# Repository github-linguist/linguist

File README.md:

# Linguist

This library is used on GitHub.com to detect blob languages, ignore binary or vendored files, suppress generated files in diffs, and generate language breakdown graphs.

## Documentation

- [How Linguist works](/docs/how-linguist-works.md)
- [Change Linguist's behaviour with overrides](/docs/overrides.md)
- [Troubleshooting](/docs/troubleshooting.md)
- [Contributing guidelines](CONTRIBUTING.md)

## Installation

Install the gem:

```bash
gem install github-linguist
```

### Dependencies

Linguist is a Ruby library so you will need a recent version of Ruby installed.
There are known problems with the macOS/Xcode supplied version of Ruby that causes problems installing some of the dependencies.
Accordingly, we highly recommend you install a version of Ruby using Homebrew, `rbenv`, `rvm`, `ruby-build`, `asdf` or other packaging system, before attempting to install Linguist and the dependencies.

Linguist uses [`charlock_holmes`](https://github.com/brianmario/charlock_holmes) for character encoding and [`rugged`](https://github.com/libgit2/rugged) for libgit2 bindings for Ruby.
These components have their own dependencies.

1. charlock_holmes
    * cmake
    * pkg-config
    * [ICU](http://site.icu-project.org/)
    * [zlib](https://zlib.net/)
2. rugged
    * [libcurl](https://curl.haxx.se/libcurl/)
    * [OpenSSL](https://www.openssl.org)

You may need to install missing dependencies before you can install Linguist.
For example, on macOS with [Homebrew](http://brew.sh/):

```bash
brew install cmake pkg-config icu4c
```

On Ubuntu:

```bash
sudo apt-get install build-essential cmake pkg-config libicu-dev zlib1g-dev libcurl4-openssl-dev libssl-dev ruby-dev
```

## Usage

### Application usage

Linguist can be used in your application as follows:

```ruby
require 'rugged'
require 'linguist'

repo = Rugged::Repository.new('.')
project = Linguist::Repository.new(repo, repo.head.target_id)
project.language       #=> "Ruby"
project.languages      #=> { "Ruby" => 119387 }
```

### Command line usage

The `github-linguist` executable operates in two distinct modes:

1. **[Git Repository mode](#git-repository)** - Analyzes an entire Git repository (when given a directory path or no path)
2. **[Single file mode](#single-file)** - Analyzes a specific file (when given a file path)

#### Git Repository

A repository's languages stats can be assessed from the command line using the `github-linguist` executable.
Without any options, `github-linguist` will output the language breakdown by percentage and file size.

```bash
cd /path-to-repository
github-linguist
```

You can try running `github-linguist` on the root directory in this repository itself:

```console
$ github-linguist
66.84%  264519     Ruby
24.68%  97685      C
6.57%   25999      Go
1.29%   5098       Lex
0.32%   1257       Shell
0.31%   1212       Dockerfile
```

#### Additional options

##### `--rev REV`

The `--rev REV` flag will change the git revision being analyzed to any [gitrevisions(1)](https://git-scm.com/docs/gitrevisions#_specifying_revisions) compatible revision you specify.

This is useful to analyze the makeup of a repo as of a certain tag, or in a certain branch.

For example, here is the popular [Jekyll open source project](https://github.com/jekyll/jekyll).

```console
$ github-linguist jekyll

70.64%  709959     Ruby
23.04%  231555     Gherkin
3.80%   38178      JavaScript
1.19%   11943      HTML
0.79%   7900       Shell
0.23%   2279       Dockerfile
0.13%   1344       Earthly
0.10%   1019       CSS
0.06%   606        SCSS
0.02%   234        CoffeeScript
0.01%   90         Hack
```

And here is Jekyll's published website, from the gh-pages branch inside their repository.

```console
$ github-linguist jekyll --rev origin/gh-pages
100.00% 2568354    HTML
```

##### `--breakdown`

The `--breakdown` or `-b` flag will additionally show the breakdown of files by language.

You can try running `github-linguist` on the root directory in this repository itself:

```console
$ github-linguist --breakdown
66.84%  264519     Ruby
24.68%  97685      C
6.57%   25999      Go
1.29%   5098       Lex
0.32%   1257       Shell
0.31%   1212       Dockerfile

Ruby:
Gemfile
Rakefile
bin/git-linguist
bin/github-linguist
ext/linguist/extconf.rb
github-linguist.gemspec
lib/linguist.rb
…
```

##### `--strategies`

The `--strategies` or `-s` flag will show the language detection strategy used for each file. This is useful for understanding how Linguist determined the language of specific files. Note that unless the `--json` flag is specified, this flag will set the `--breakdown` flag implicitly.

You can try running `github-linguist` on the root directory in this repository itself with the strategies flag:

```console
$ github-linguist --breakdown --strategies
66.84%  264519     Ruby
24.68%  97685      C
6.57%   25999      Go
1.29%   5098       Lex
0.32%   1257       Shell
0.31%   1212       Dockerfile

Ruby:
  Gemfile [Filename]
  Rakefile [Filename]
  bin/git-linguist [Extension]
  bin/github-linguist [Extension]
  lib/linguist.rb [Extension]
  …
```

If a file's language is affected by `.gitattributes`, the strategy will show the original detection method along with a note indicating whether the gitattributes setting changed the result or confirmed it.

For instance, if you had the following .gitattributes overrides in your repo:

```gitattributes

*.ts linguist-language=JavaScript
*.js linguist-language=JavaScript

```

the output of Linguist would be something like this:

```console
100.00% 217        JavaScript

JavaScript:
  demo.ts [Heuristics (overridden by .gitattributes)]
  demo.js [Extension (confirmed by .gitattributes)]
```

##### `--json`

The `--json` or `-j` flag output the data into JSON format.

```console
$ github-linguist --json
{"Dockerfile":{"size":1212,"percentage":"0.31"},"Ruby":{"size":264519,"percentage":"66.84"},"C":{"size":97685,"percentage":"24.68"},"Lex":{"size":5098,"percentage":"1.29"},"Shell":{"size":1257,"percentage":"0.32"},"Go":{"size":25999,"percentage":"6.57"}}
```

This option can be used in conjunction with `--breakdown` to get a full list of files along with the size and percentage data.

```console
$ github-linguist --breakdown --json
{"Dockerfile":{"size":1212,"percentage":"0.31","files":["Dockerfile","tools/grammars/Dockerfile"]},"Ruby":{"size":264519,"percentage":"66.84","files":["Gemfile","Rakefile","bin/git-linguist","bin/github-linguist","ext/linguist/extconf.rb","github-linguist.gemspec","lib/linguist.rb",...]}}

```

NB. The `--strategies` flag has no effect, when the `--json` flag is present.

#### Single file

Alternatively you can find stats for a single file using the `github-linguist` executable.

You can try running `github-linguist` on files in this repository itself:

```console
$ github-linguist grammars.yml
grammars.yml: 884 lines (884 sloc)
  type:      Text
  mime type: text/x-yaml
  language:  YAML
```

#### Additional options

##### `--breakdown`

This flag has no effect in *Single file* mode.

##### `--strategies`

When using the `--strategies` or `-s` flag with a single file, you can see which detection method was used:

```console
$ github-linguist --strategies lib/linguist.rb 
lib/linguist.rb: 105 lines (96 sloc)
  type:      Text
  mime type: application/x-ruby
  language:  Ruby
  strategy:  Extension
```

If a file's language is affected by `.gitattributes`, the strategy will show whether the gitattributes setting changed the result or confirmed it:

In this fictitious example, it says "confirmed by .gitattributes" since the detection process (using the Filename strategy) would have given the same output as the override:
```console
.devcontainer/devcontainer.json: 27 lines (27 sloc)
  type:      Text
  mime type: application/json
  language:  JSON with Comments
  strategy:  Filename (confirmed by .gitattributes)
```

In this other fictitious example, it says "overridden by .gitattributes" since the gitattributes setting changes the detected language to something different:

```console
test.rb: 13 lines (11 sloc)
  type:      Text
  mime type: application/x-ruby
  language:  Java
  strategy:  Extension (overridden by .gitattributes)
```

Here, the `.rb` file would normally be detected as Ruby by the Extension strategy, but `.gitattributes` overrides it to be detected as Java instead.

##### `--json`

Using the `--json` flag will give you the output for a single file in JSON format:

```console
$ github-linguist --strategies --json  lib/linguist.rb
{"lib/linguist.rb":{"lines":105,"sloc":96,"type":"Text","mime_type":"application/x-ruby","language":"Ruby","large":false,"generated":false,"vendored":false}}
```

NB. The `--strategies` has no effect, when the `--json` flag is present.

#### Docker

If you have Docker installed you can either build or use
our pre-built images and run Linguist within a container:

```console
$ docker run --rm -v $(pwd):$(pwd):Z -w $(pwd) -t ghcr.io/github-linguist/linguist:latest
66.84%  264519     Ruby
24.68%  97685      C
6.57%   25999      Go
1.29%   5098       Lex
0.32%   1257       Shell
0.31%   1212       Dockerfile
```

##### Building the image

```console
$ docker build -t linguist .
$ docker run --rm -v $(pwd):$(pwd):Z -w $(pwd) -t linguist
66.84%  264519     Ruby
24.68%  97685      C
6.57%   25999      Go
1.29%   5098       Lex
0.32%   1257       Shell
0.31%   1212       Dockerfile
$ docker run --rm -v $(pwd):$(pwd) -w $(pwd) -t linguist github-linguist --breakdown
66.84%  264519     Ruby
24.68%  97685      C
6.57%   25999      Go
1.29%   5098       Lex
0.32%   1257       Shell
0.31%   1212       Dockerfile

Ruby:
Gemfile
Rakefile
bin/git-linguist
bin/github-linguist
ext/linguist/extconf.rb
github-linguist.gemspec
lib/linguist.rb
…
```

## Contributing

Please check out our [contributing guidelines](CONTRIBUTING.md).

## License

The language grammars included in this gem are covered by their repositories' respective licenses.
[`vendor/README.md`](/vendor/README.md) lists the repository for each grammar.

All other files are covered by the MIT license, see [`LICENSE`](./LICENSE).

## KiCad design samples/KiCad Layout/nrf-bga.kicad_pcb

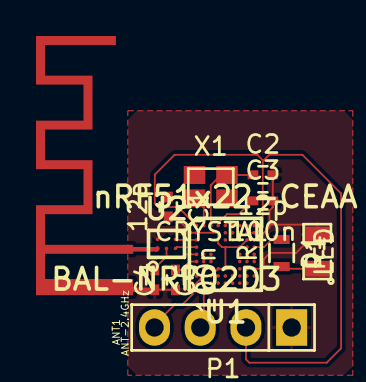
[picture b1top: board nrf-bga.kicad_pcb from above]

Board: 2 copper layers, 12 parts (0 on the bottom side), 14 nets.

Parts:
ANT1: ANT-2.4GHz
C1, C2: 12p; C_0402
C3, C4: 100n; C_0402
C5: 2n2; C_0402
D1: LED; SMD-0805
P1: CONN_01X04; Pin_Header_Straight_1x04
R1: R; R_0603
U1: nRF51x22-CEAA; WLCSP62
U2: BAL-NRF02D3
X1: CRYSTAL; CX2520DB

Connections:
+BATT: P1.2, U1.A1, U1.B8, U1.B9
GND: ANT1.1, C1.2, C2.2, C3.2, C4.1, C5.2, D1.2, P1.1, U1.B1, U1.B4, U1.C8, U1.C9, U1.D7, U1.G4, U1.G5, U1.G6, U1.G9, U1.H3, U2.B1
LED: R1.1, U1.D9
unnamed: ANT1.2, U2.A1
unnamed: C1.1, U1.A2, X1.1
unnamed: C2.1, U1.A3, X1.2
unnamed: C3.1, U1.A4
unnamed: C4.2, U1.F1
unnamed: C5.1, U1.E1, U2.A2
unnamed: D1.1, R1.2
unnamed: U1.C1, U2.B3
unnamed: U1.D1, U2.A3
SWCLK: P1.4, U1.H2
SWDIO: P1.3, U1.J2

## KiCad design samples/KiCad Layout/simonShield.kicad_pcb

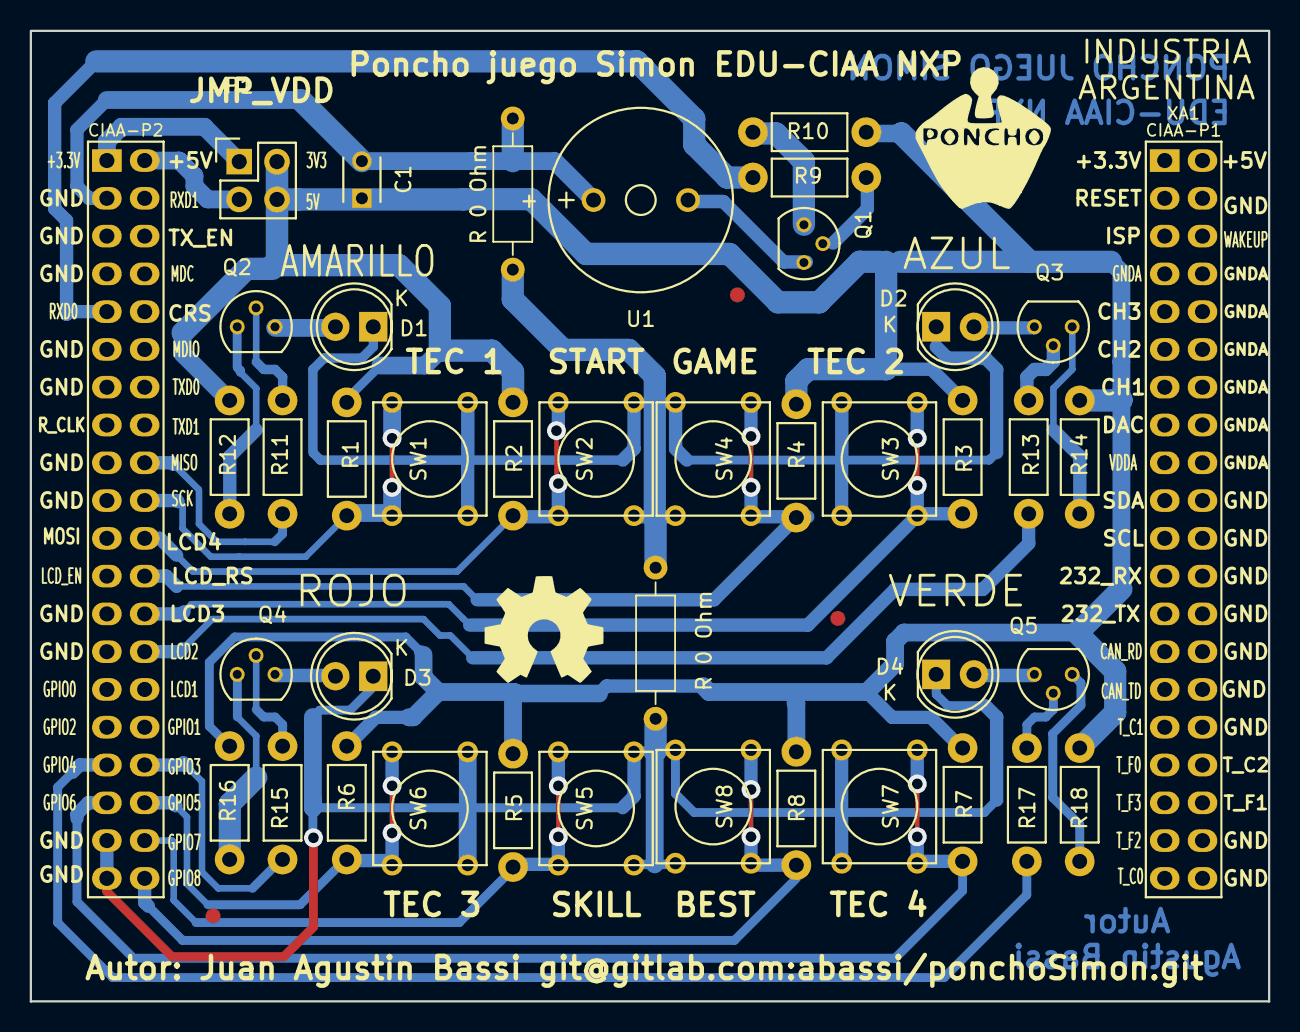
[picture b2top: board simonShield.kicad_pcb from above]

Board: 2 copper layers, 83.2 x 65.2 mm, 45 parts (0 on the bottom side), 32 nets.

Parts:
C1: C_100nF; C_Disc_D3_P2.5
D1: AMARILLO; LED-5MM
D2: AZUL; LED-5MM
D3: ROJO; LED-5MM
D4: VERDE; LED-5MM
F1, F2, F3: FIDUCIAL; Fiducial_1mm
G101: Logo_OSHWA
P1: PWR_JUMPER; Pin_Header_Straight_2x02
Q1, Q2, Q3, Q4, Q5: BC547; TO-92_Molded_Narrow
R1, R2, R3, R4, R5, R6, R7, R8, R9: 3K3; Resistor_Horizontal_RM7mm
R10: 1K; Resistor_Horizontal_RM7mm
R11, R13, R15, R17: 10K; Resistor_Horizontal_RM7mm
R12, R14, R16, R18: 680; Resistor_Horizontal_RM7mm
R 0 Ohm, R 0 Ohm#2: R; R_Axial_DIN0207_L6.3mm_D2.5mm_P10.16mm_Horizontal
SW1, SW2, SW3, SW4, SW5, SW6, SW7, SW8: SW_PUSH; SW_PUSH_SMALL
U1: BUZZER; MagneticBuzzer_ProSignal_ABT-410-RC
XA1: Conn_Poncho2P_2x_20x2; Conn_Poncho_SinBorde

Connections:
/buttons/BTN_CFG_1: R2.1, SW2.1, XA1.62
/buttons/BTN_CFG_2: R4.1, SW4.1, XA1.64
/buttons/BTN_CFG_3: R6.1, SW6.1, XA1.76
/buttons/BTN_CFG_4: R8.1, SW8.1, XA1.80
/buttons/BTN_LED_1: R1.1, SW1.1, XA1.60
/buttons/BTN_LED_2: R3.1, SW3.1, XA1.66
/buttons/BTN_LED_3: R5.1, SW5.1, XA1.78
/buttons/BTN_LED_4: R7.1, SW7.1, XA1.75
/ciaaConector/LED_1: R11.1, XA1.58
/ciaaConector/LED_2: R13.1, XA1.68
/ciaaConector/LED_3: R15.1, XA1.74
/ciaaConector/LED_4: R17.1, XA1.73
/ciaaConector/PWM: R9.2, XA1.49
GND: C1.2, D1.1, D2.1, D3.1, D4.1, R 0 Ohm.1, R 0 Ohm.2, R 0 Ohm#2.1, R 0 Ohm#2.2, SW1.2, SW2.2, SW3.2, SW4.2, SW5.2, SW6.2, SW7.2, SW8.2, U1.2, XA1.43, XA1.77, XA1.79
unnamed: D1.2, Q2.3
unnamed: D2.2, Q3.3
unnamed: D3.2, Q4.3
unnamed: D4.2, Q5.3
unnamed: P1.1, XA1.41
unnamed: P1.3, XA1.42
unnamed: Q1.1, R10.2
unnamed: Q1.2, R9.1
unnamed: Q1.3, U1.1
unnamed: Q2.1, R12.1
unnamed: Q2.2, R11.2
unnamed: Q3.1, R14.1
unnamed: Q3.2, R13.2
unnamed: Q4.1, R16.1
unnamed: Q4.2, R15.2
unnamed: Q5.1, R18.1
unnamed: Q5.2, R17.2
VCC: C1.1, P1.2, P1.4, R1.2, R2.2, R3.2, R4.2, R5.2, R6.2, R7.2, R8.2, R10.1, R12.2, R14.2, R16.2, R18.2
